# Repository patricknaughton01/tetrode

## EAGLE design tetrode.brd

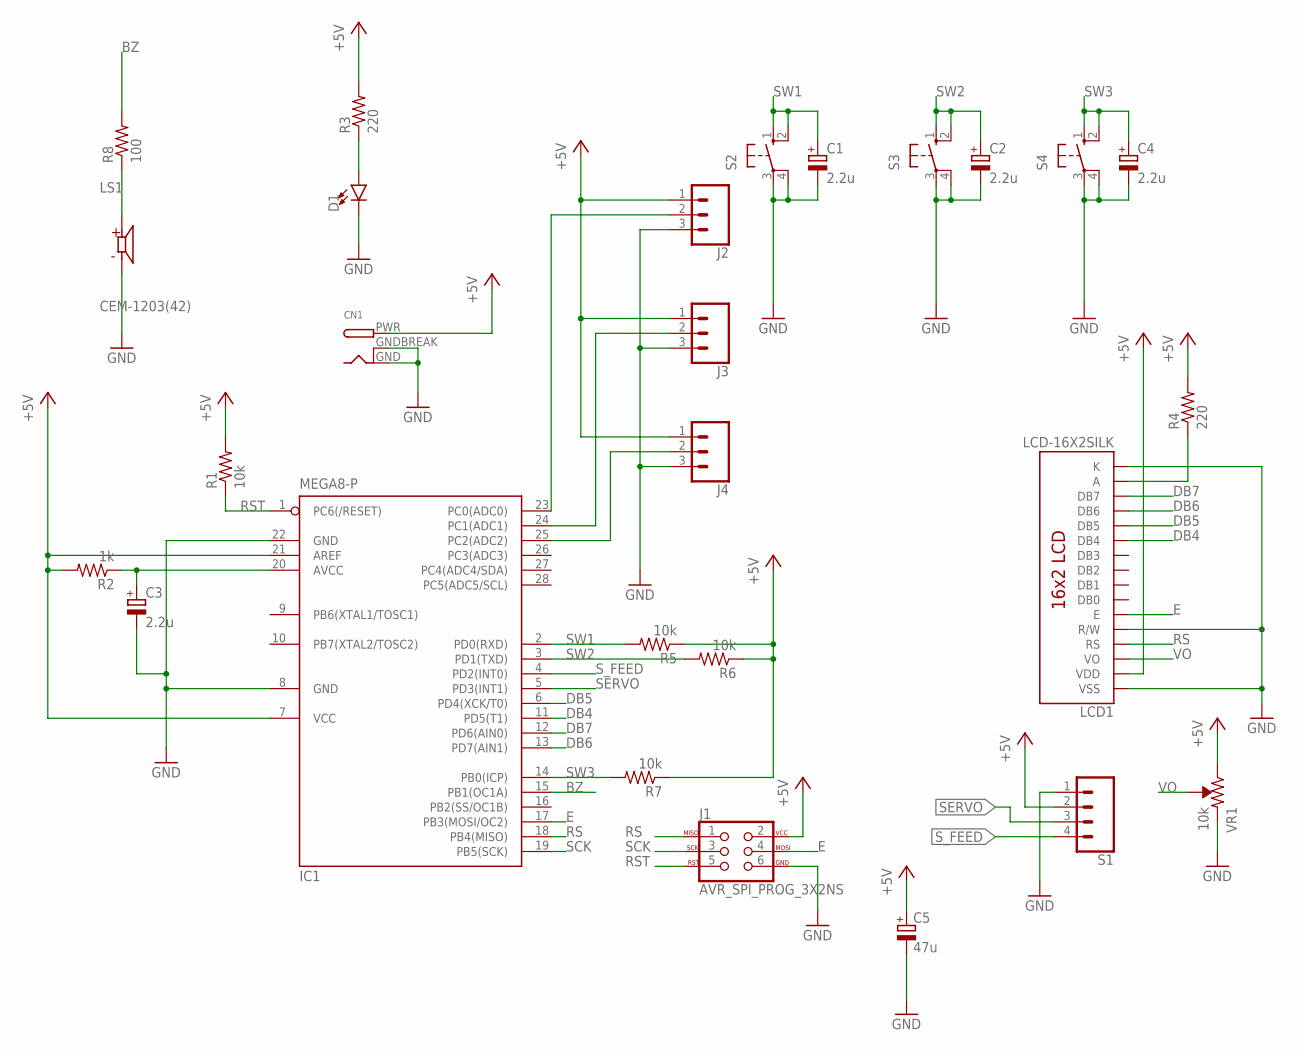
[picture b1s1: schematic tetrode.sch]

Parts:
C1, C2, C3, C4: 2.2u; E2-5
C5: 47u; E2,5-6
CN1: DCBARRELPTH; DCJACK_2MM_PTH
D1: LED-3MM-NO_SILK; LED_3MM-NS
IC1: MEGA8-P; DIL28-3
J1: AVR_SPI_PROG_3X2NS; 2X3-NS
J2, J3, J4: CONN_03; 1X03
LCD1: LCD-16X2SILK; LCD-16X2
LS1: CEM-1203(42); CUI_CEM-1203(42)
R1, R5, R6, R7: 10k; 0309/10
R2: 1k; 0309/10
R3, R4: 220; 0309/10
R8: 100; 0309/10
S1: CONN_04; 1X04
S2, S3, S4: 40-XX; B3F-40XX
VR1: 10k; TRIMPOT-PTH-3386U

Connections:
+5V: C5.+, CN1.PWR, IC1.7 (VCC), IC1.21 (AREF), J1.2, J2.1, J3.1, J4.1, LCD1.2 (VDD), R1.2, R2.2, R3.2, R4.2, R5.1, R6.1, R7.1, S1.2, VR1.3 (CW)
BZ: IC1.15 (PB1(OC1A)), R8.2
DB4: IC1.11 (PD5(T1)), LCD1.11 (DB4)
DB5: IC1.6 (PD4(XCK/T0)), LCD1.12 (DB5)
DB6: IC1.13 (PD7(AIN1)), LCD1.13 (DB6)
DB7: IC1.12 (PD6(AIN0)), LCD1.14 (DB7)
E: IC1.17 (PB3(MOSI/OC2)), J1.4, LCD1.6 (E)
GND: C1.-, C2.-, C3.-, C4.-, C5.-, CN1.GND, CN1.GNDBREAK, D1.K (C), IC1.8 (GND), IC1.22 (GND), J1.6, J2.3, J3.3, J4.3, LCD1.1 (VSS), LCD1.5 (R/W), LCD1.16 (K), LS1.N, S1.1, S2.3, S2.4 (P1), S3.3, S3.4 (P1), S4.3, S4.4 (P1), VR1.1 (CCW)
unnamed: IC1.23 (PC0(ADC0)), J2.2
unnamed: D1.A, R3.1
unnamed: IC1.24 (PC1(ADC1)), J3.2
unnamed: IC1.25 (PC2(ADC2)), J4.2
unnamed: C3.+, IC1.20 (AVCC), R2.1
unnamed: LS1.P, R8.1
unnamed: LCD1.15 (A), R4.1
RS: IC1.18 (PB4(MISO)), J1.1, LCD1.4 (RS)
RST: IC1.1 (PC6(/RESET)), J1.5, R1.1
SCK: IC1.19 (PB5(SCK)), J1.3
SERVO: IC1.5 (PD3(INT1)), S1.3
SW1: C1.+, IC1.2 (PD0(RXD)), R5.2, S2.1 (S), S2.2 (S1)
SW2: C2.+, IC1.3 (PD1(TXD)), R6.2, S3.1 (S), S3.2 (S1)
SW3: C4.+, IC1.14 (PB0(ICP)), R7.2, S4.1 (S), S4.2 (S1)
S_FEED: IC1.4 (PD2(INT0)), S1.4
VO: LCD1.3 (VO), VR1.2 (WIPER)

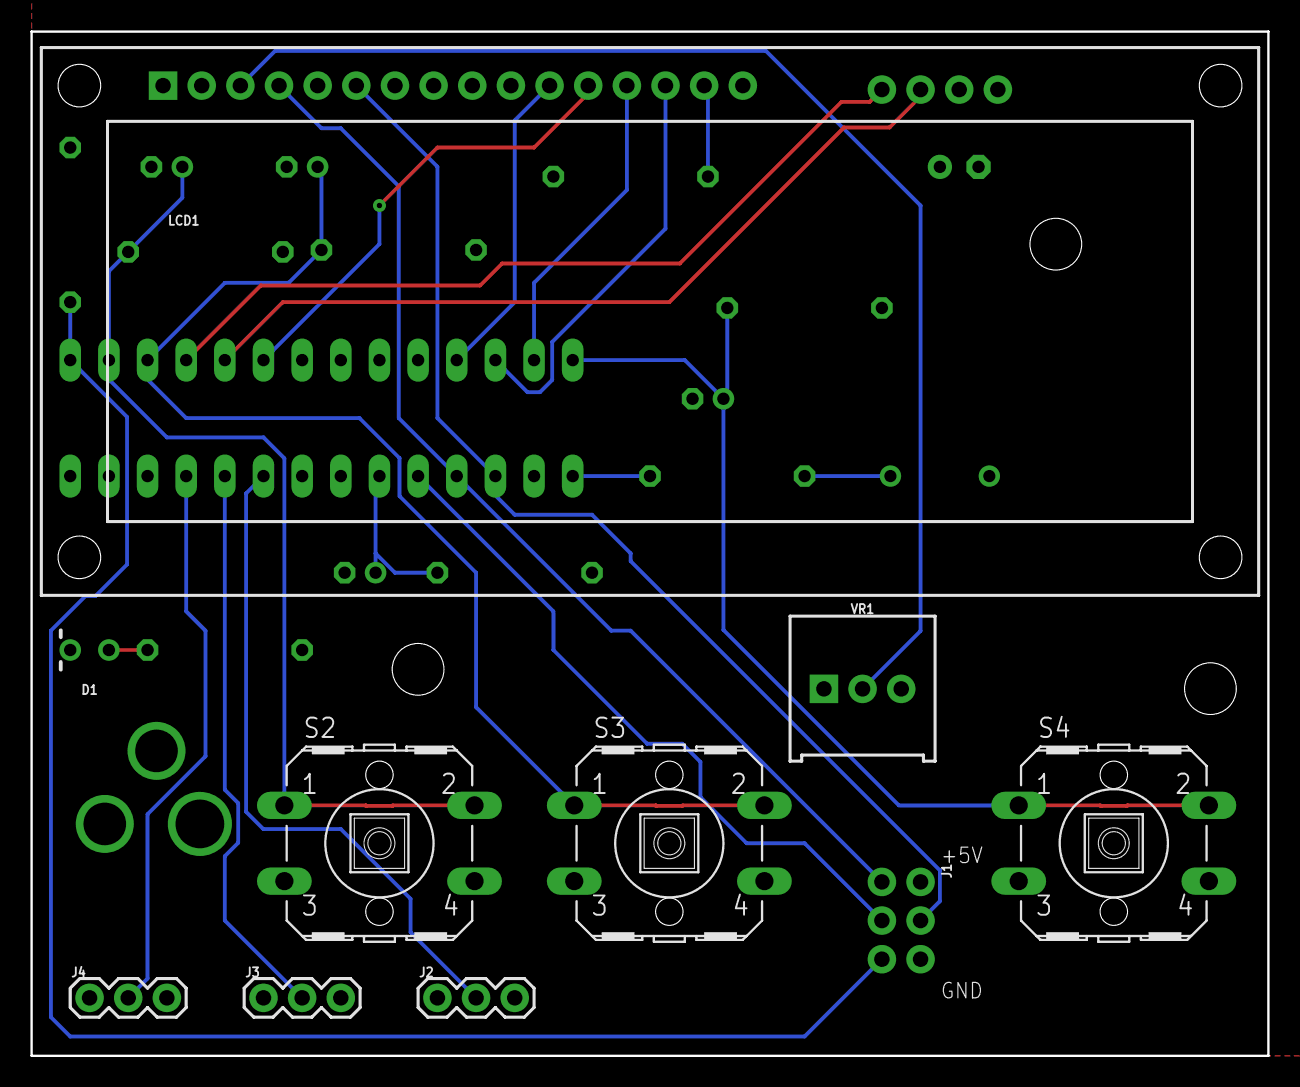
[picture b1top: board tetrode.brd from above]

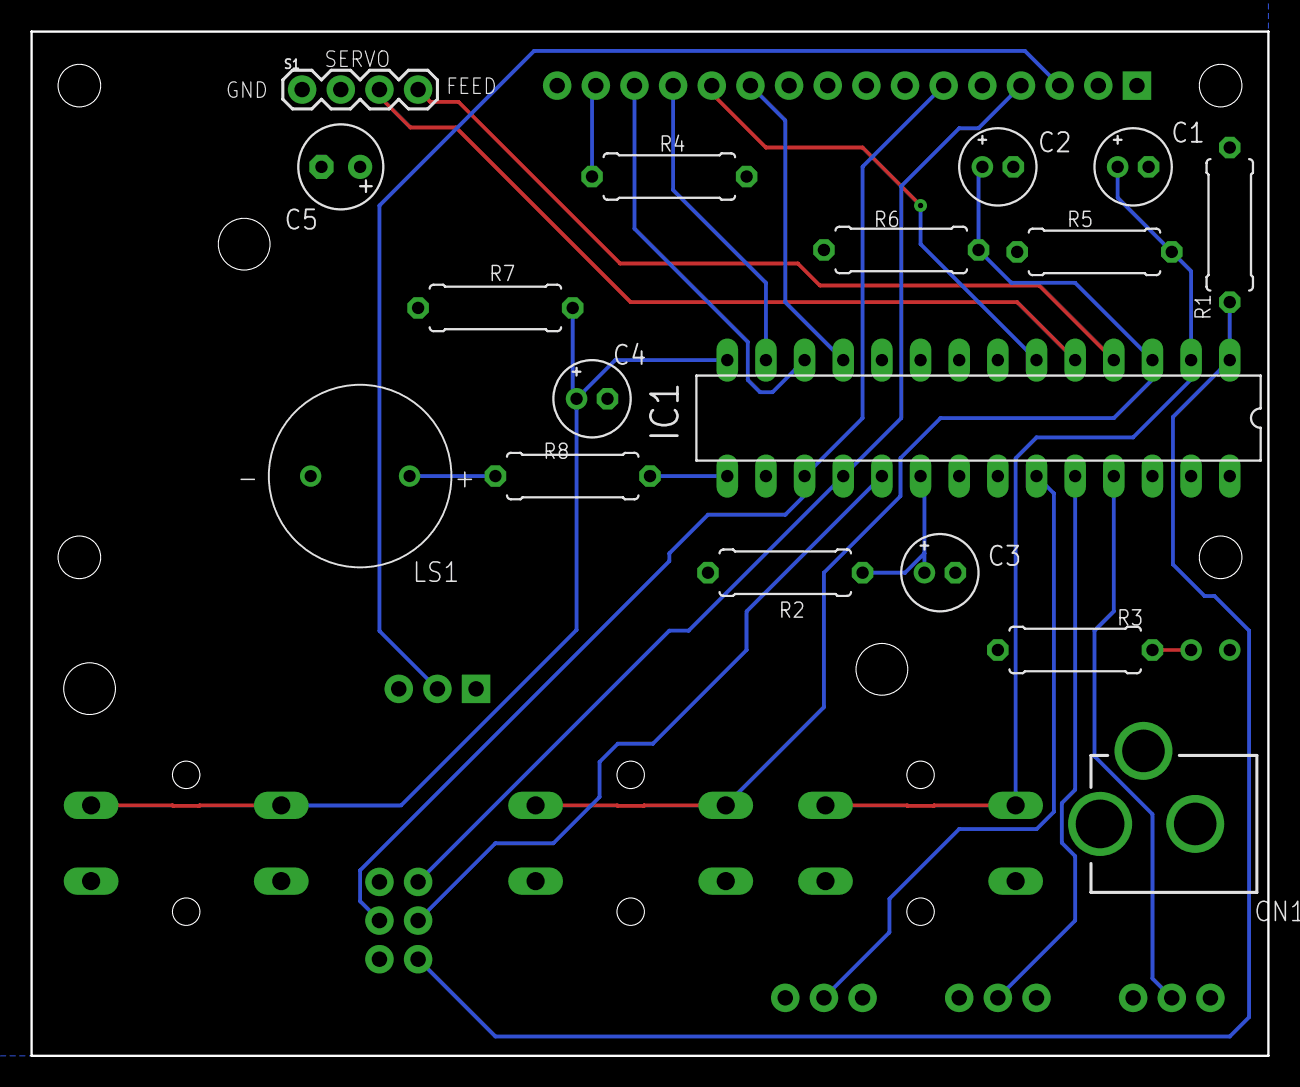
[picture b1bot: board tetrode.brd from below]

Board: 2 copper layers, 81.3 x 67.3 mm, 27 parts (17 on the bottom side), 24 nets.

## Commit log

2020-07-16 Started code
2020-07-30 Updates to CAD for board and base, started on code
2020-07-31 Started CAD for board
2020-07-31 First draft of FSM for controlling drive
2020-07-31 Seem to have made rotation counting more robust
2020-07-31 First draft of code
2020-07-31 Interface updates
2020-08-01 Changed pin for a button
2020-08-06 Switched layout of board and reduced max speed of servo to resolve brown out when the servo stops
2020-08-06 Improved rotation tracking to include fractions of a rotation and do it better
2022-11-14 Updated code

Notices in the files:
parts and their libraries:
SparkFun-LED: Licensing: Creative Commons ShareAlike 4.0 International - https://creativecommons.org/licenses/by-sa/4.0
